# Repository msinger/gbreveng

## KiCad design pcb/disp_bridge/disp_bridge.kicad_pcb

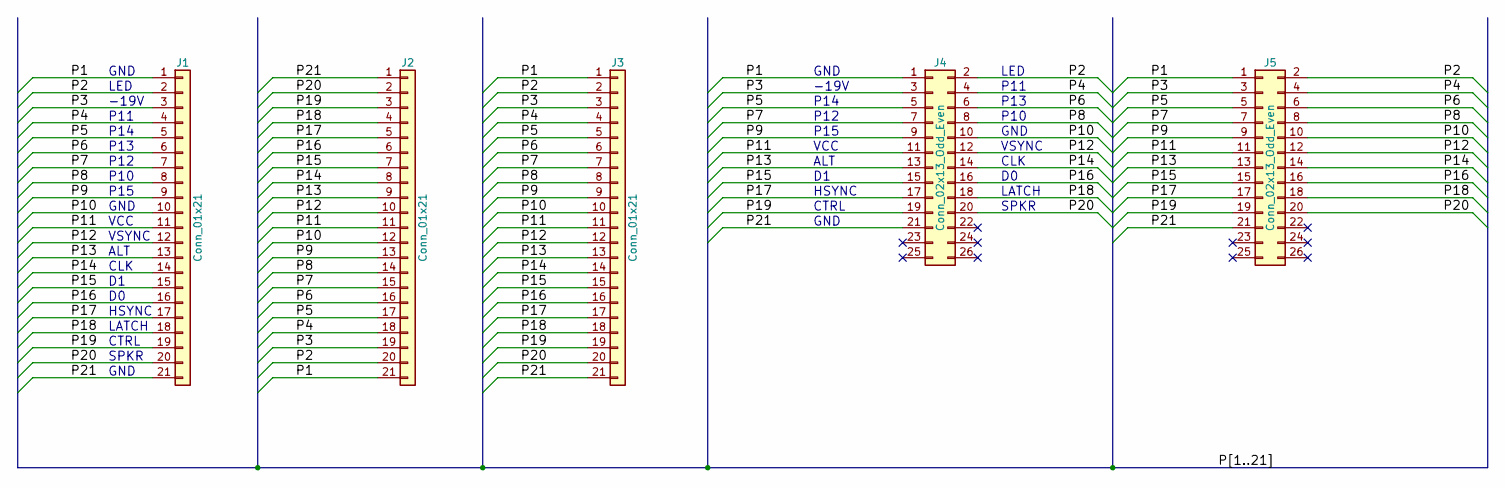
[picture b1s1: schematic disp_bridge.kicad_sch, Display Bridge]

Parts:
J1, J2, J3: Conn_01x21; DMG_FFC_LCD-Board_21Pin
J4, J5: Conn_02x13_Odd_Even; PinHeader_2x13_P2.54mm_Vertical

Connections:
/P1: J1.1, J2.21, J3.1, J4.1, J5.1
/P2: J1.2, J2.20, J3.2, J4.2, J5.2
/P3: J1.3, J2.19, J3.3, J4.3, J5.3
/P4: J1.4, J2.18, J3.4, J4.4, J5.4
/P5: J1.5, J2.17, J3.5, J4.5, J5.5
/P6: J1.6, J2.16, J3.6, J4.6, J5.6
/P7: J1.7, J2.15, J3.7, J4.7, J5.7
/P8: J1.8, J2.14, J3.8, J4.8, J5.8
/P9: J1.9, J2.13, J3.9, J4.9, J5.9
/P10: J1.10, J2.12, J3.10, J4.10, J5.10
/P11: J1.11, J2.11, J3.11, J4.11, J5.11
/P12: J1.12, J2.10, J3.12, J4.12, J5.12
/P13: J1.13, J2.9, J3.13, J4.13, J5.13
/P14: J1.14, J2.8, J3.14, J4.14, J5.14
/P15: J1.15, J2.7, J3.15, J4.15, J5.15
/P16: J1.16, J2.6, J3.16, J4.16, J5.16
/P17: J1.17, J2.5, J3.17, J4.17, J5.17
/P18: J1.18, J2.4, J3.18, J4.18, J5.18
/P19: J1.19, J2.3, J3.19, J4.19, J5.19
/P20: J1.20, J2.2, J3.20, J4.20, J5.20
/P21: J1.21, J2.1, J3.21, J4.21, J5.21

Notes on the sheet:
SPKR
LATCH
P15
VSYNC
P11
P13
GND
P14
HSYNC
P12
-19V
VCC
P10
CLK
ALT
LED
CTRL

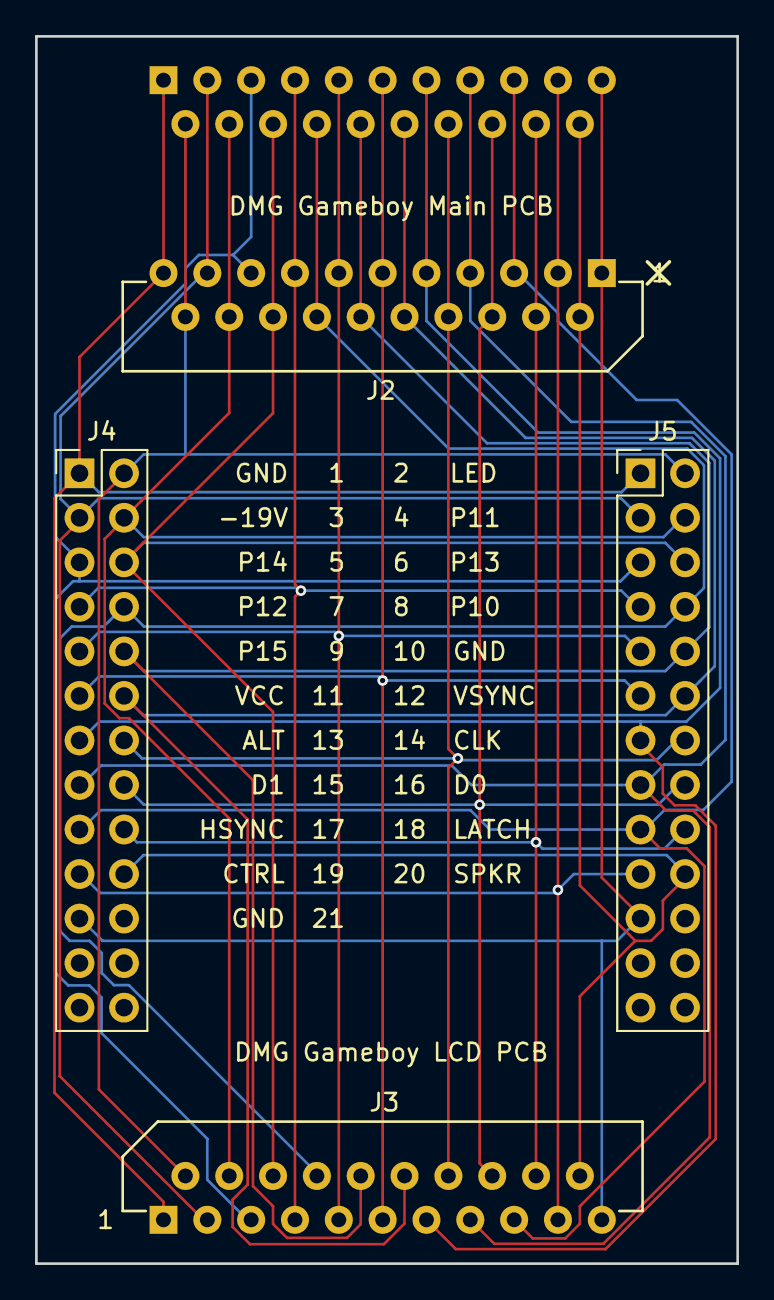
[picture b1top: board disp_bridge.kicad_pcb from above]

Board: 2 copper layers, 40.0 x 70.0 mm, 5 parts (1 on the bottom side), 21 nets.

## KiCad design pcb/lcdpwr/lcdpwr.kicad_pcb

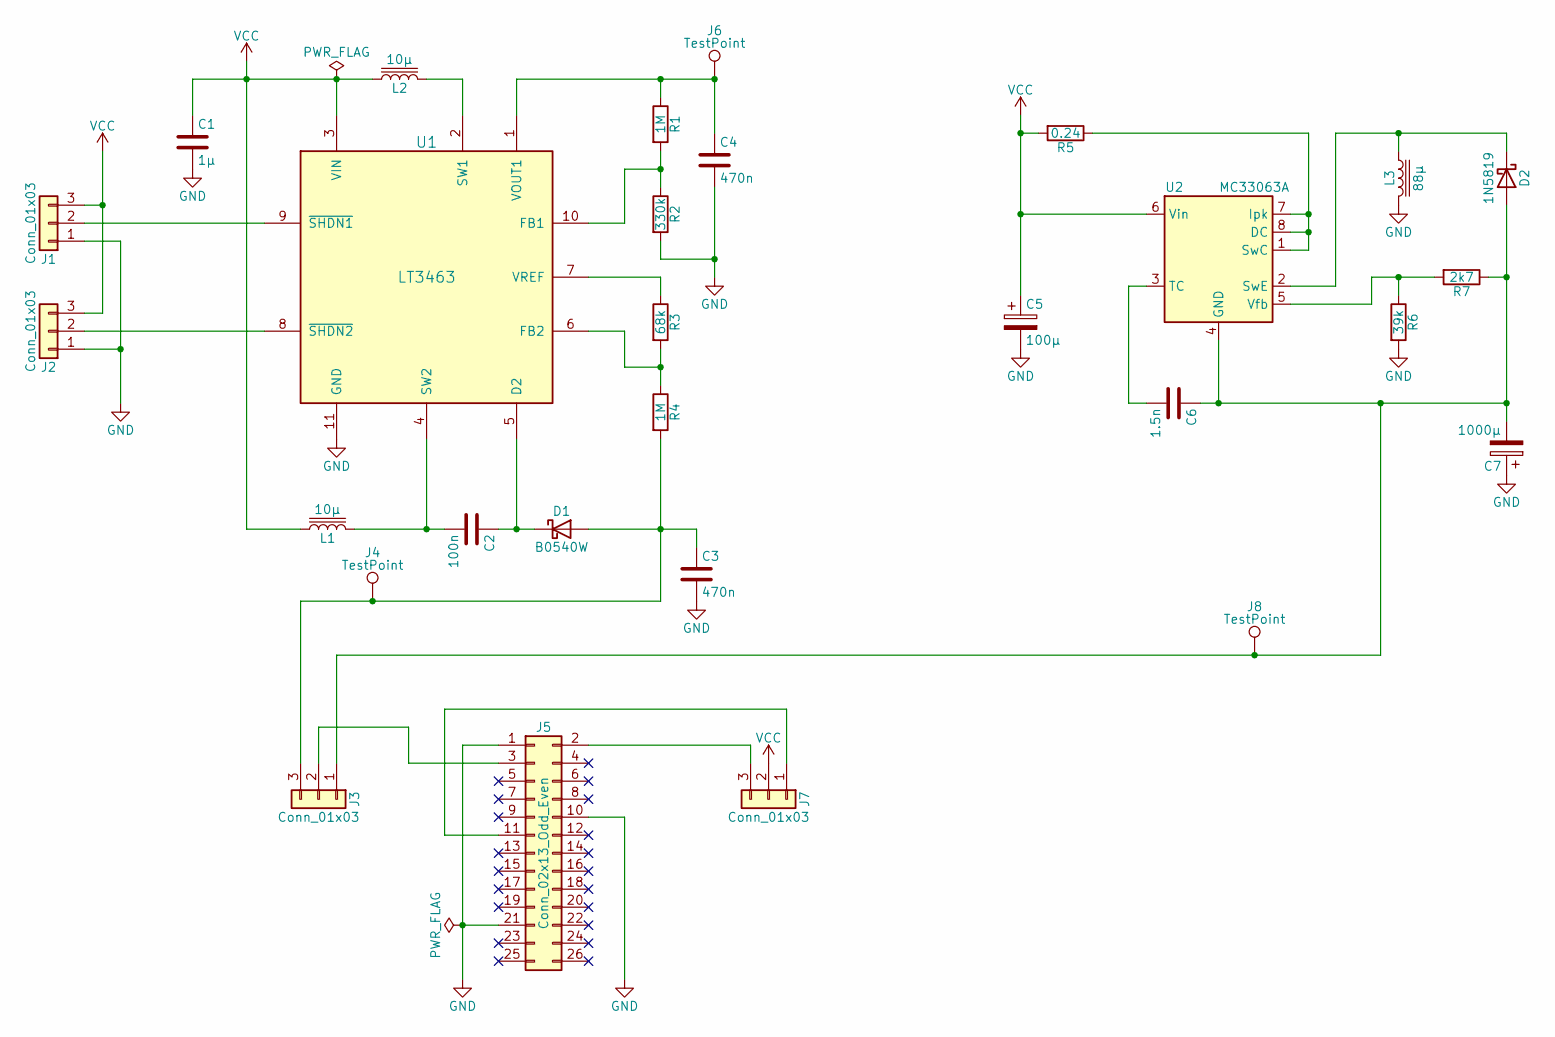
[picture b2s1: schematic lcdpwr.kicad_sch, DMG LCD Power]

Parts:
C1: 1µ; C_Disc_D4.3mm_W1.9mm_P5.00mm
C2: 100n; C_Disc_D3.0mm_W1.6mm_P2.50mm
C3, C4: 470n; C_Rect_L13.0mm_W4.0mm_P10.00mm_FKS3_FKP3_MKS4
C5: 100µ; CP_Radial_D5.0mm_P2.50mm
C6: 1.5n; C_Disc_D4.3mm_W1.9mm_P5.00mm
C7: 1000µ; CP_Radial_D10.0mm_P5.00mm
D1: B0540W; D_SOD-123
D2: 1N5819; D_A-405_P10.16mm_Horizontal
J1, J2, J3, J7: Conn_01x03; PinHeader_1x03_P2.54mm_Vertical
J4, J6, J8: TestPoint; TestPoint_Keystone_5010-5014_Multipurpose
J5: Conn_02x13_Odd_Even; PinHeader_2x13_P2.54mm_Vertical
L1, L2: 10µ; L_Radial_D7.0mm_P3.00mm
L3: 88µ; L_Radial_D12.5mm_P7.00mm_Fastron_09HCP
R1, R4: 1M; R_Axial_DIN0207_L6.3mm_D2.5mm_P10.16mm_Horizontal
R2: 330k; R_Axial_DIN0207_L6.3mm_D2.5mm_P10.16mm_Horizontal
R3: 68k; R_Axial_DIN0207_L6.3mm_D2.5mm_P10.16mm_Horizontal
R5: 0.24; R_Axial_DIN0411_L9.9mm_D3.6mm_P12.70mm_Horizontal
R6: 39k; R_Axial_DIN0207_L6.3mm_D2.5mm_P10.16mm_Horizontal
R7: 2k7; R_Axial_DIN0207_L6.3mm_D2.5mm_P10.16mm_Horizontal
U1: LT3463; DFN-10-1EP_3x3mm_P0.5mm_EP1.55x2.48mm
U2: MC33063A; DIP-8_W7.62mm_Socket_LongPads

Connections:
GND: C1.2, C3.2, C4.2, C5.2, C7.1, J1.1, J2.1, J5.1, J5.10, J5.21, L3.2, R2.2, R6.2, U1.11 (GND)
unnamed: C3.1, D1.2 (A), J3.3, J4.1, R4.2
unnamed: C2.1, D1.1 (K), U1.5 (D2)
unnamed: C6.1, C7.2, D2.2 (A), J3.1, J8.1, R7.1, U2.4 (GND)
unnamed: D2.1 (K), L3.1, U2.2 (SwE)
unnamed: J1.2, U1.9 (~SHDN1)
unnamed: J2.2, U1.8 (~SHDN2)
unnamed: J3.2, J5.3
unnamed: J5.2, J7.3
unnamed: J5.11, J7.1
unnamed: R1.2, R2.1, U1.10 (FB1)
unnamed: R3.2, R4.1, U1.6 (FB2)
unnamed: L2.2, U1.2 (SW1)
unnamed: C2.2, L1.2, U1.4 (SW2)
unnamed: C4.1, J6.1, R1.1, U1.1 (VOUT1)
unnamed: R3.1, U1.7 (VREF)
unnamed: R5.1, U2.1 (SwC), U2.7 (Ipk), U2.8 (DC)
unnamed: C6.2, U2.3 (TC)
unnamed: R6.1, R7.2, U2.5 (Vfb)
VCC: C1.1, C5.1, J1.3, J2.3, J7.2, L1.1, L2.1, R5.2, U1.3 (VIN), U2.6 (Vin)

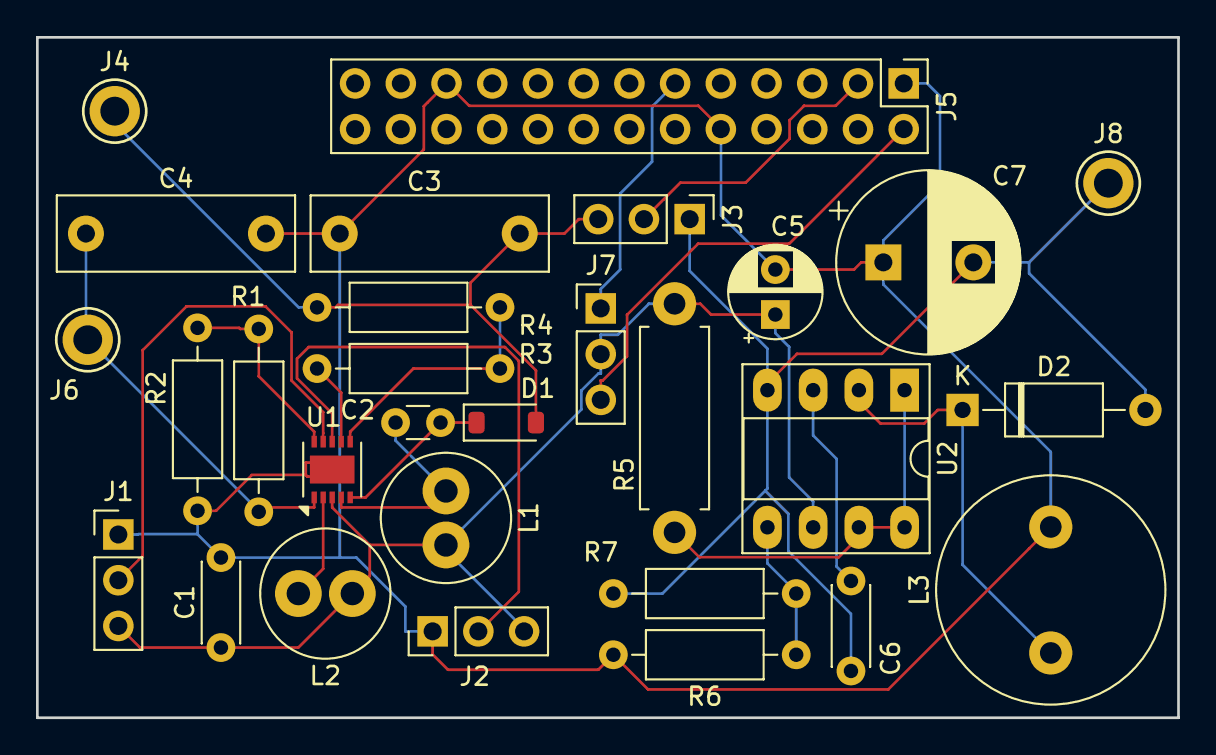
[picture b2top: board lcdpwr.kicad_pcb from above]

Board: 2 copper layers, 63.4 x 37.8 mm, 29 parts (0 on the bottom side), 20 nets.

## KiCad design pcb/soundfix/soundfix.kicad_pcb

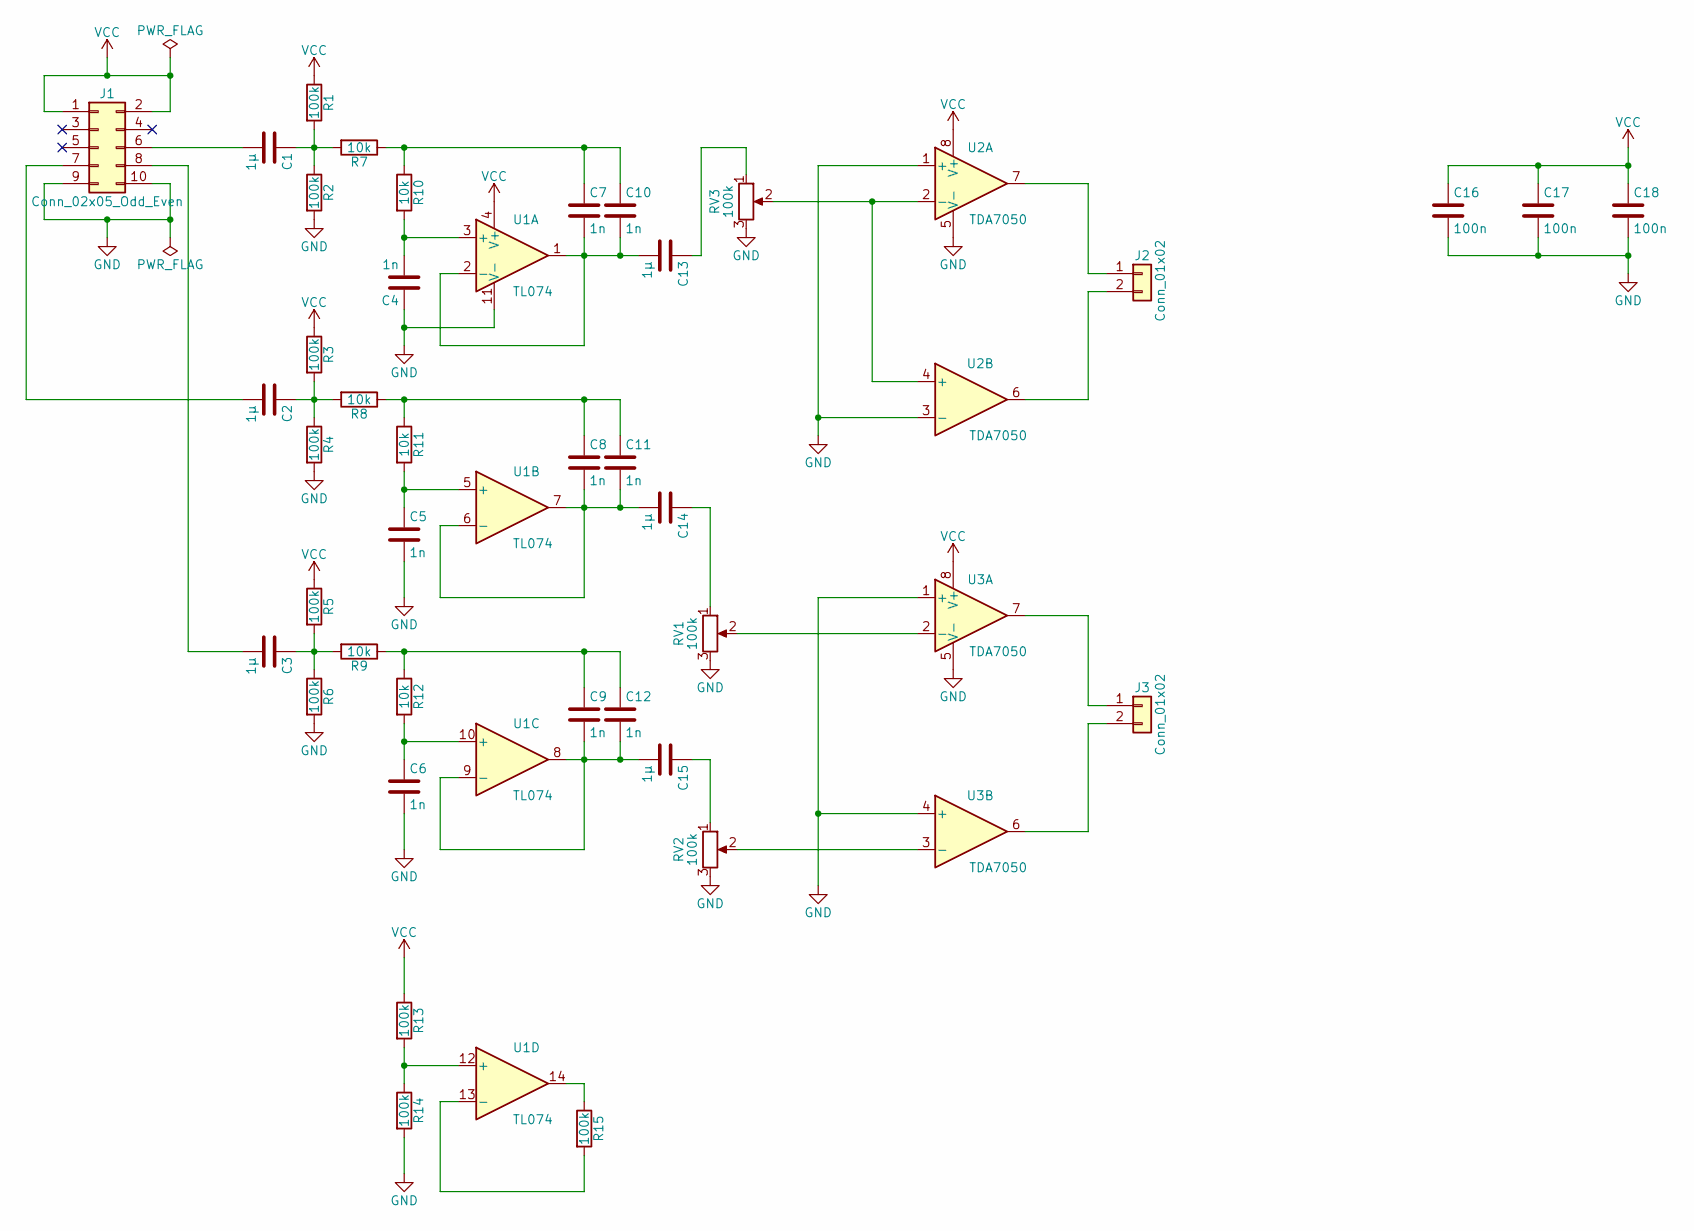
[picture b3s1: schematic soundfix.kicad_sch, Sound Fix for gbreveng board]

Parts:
C1, C2, C3, C13, C14, C15: 1µ; C_Disc_D5.0mm_W2.5mm_P5.00mm
C4, C5, C6, C7, C8, C9, C10, C11, C12: 1n; C_Disc_D3.0mm_W2.0mm_P2.50mm
C16, C17, C18: 100n; C_Disc_D3.0mm_W2.0mm_P2.50mm
J1: Conn_02x05_Odd_Even; PinSocket_2x05_P2.54mm_Vertical
J2, J3: Conn_01x02; PinHeader_1x02_P2.54mm_Vertical
R1, R2, R3, R4, R5, R6, R13, R14, R15: 100k; R_Axial_DIN0207_L6.3mm_D2.5mm_P2.54mm_Vertical
R7, R8, R9, R10, R11, R12: 10k; R_Axial_DIN0207_L6.3mm_D2.5mm_P2.54mm_Vertical
RV1, RV2, RV3: 100k; Potentiometer_ACP_CA9-H2,5_Horizontal
U1: TL074; DIP-14_W7.62mm_Socket
U2, U3: TDA7050; DIP-8_W7.62mm_Socket

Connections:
GND: C4.1, C5.2, C6.2, C16.2, C17.2, C18.2, J1.9, J1.10, R2.2, R4.2, R6.2, R14.2, RV1.3, RV2.3, RV3.3, U1.11 (V-), U2.1 (+), U2.3 (-), U2.5 (V-), U3.1 (+), U3.4 (+), U3.5 (V-)
unnamed: C1.1, R1.2, R2.1, R7.2
unnamed: C2.1, R3.2, R4.1, R8.2
unnamed: C3.1, R5.2, R6.1, R9.2
unnamed: C7.1, C10.1, R7.1, R10.1
unnamed: C8.1, C11.1, R8.1, R11.1
unnamed: C9.1, C12.1, R9.1, R12.1
unnamed: C13.1, RV3.1
unnamed: C14.1, RV1.1
unnamed: C15.1, RV2.1
unnamed: C1.2, J1.6
unnamed: C2.2, J1.7
unnamed: C3.2, J1.8
unnamed: J2.1, U2.7
unnamed: J2.2, U2.6
unnamed: J3.1, U3.7
unnamed: J3.2, U3.6
unnamed: R15.1, U1.14
unnamed: C4.2, R10.2, U1.3 (+)
unnamed: C7.2, C10.2, C13.2, U1.1, U1.2 (-)
unnamed: C5.1, R11.2, U1.5 (+)
unnamed: C8.2, C11.2, C14.2, U1.6 (-), U1.7
unnamed: C6.1, R12.2, U1.10 (+)
unnamed: C9.2, C12.2, C15.2, U1.8, U1.9 (-)
unnamed: R13.2, R14.1, U1.12 (+)
unnamed: R15.2, U1.13 (-)
unnamed: RV3.2, U2.2 (-), U2.4 (+)
unnamed: RV1.2, U3.2 (-)
unnamed: RV2.2, U3.3 (-)
VCC: C16.1, C17.1, C18.1, J1.1, J1.2, R1.1, R3.1, R5.1, R13.1, U1.4 (V+), U2.8 (V+), U3.8 (V+)

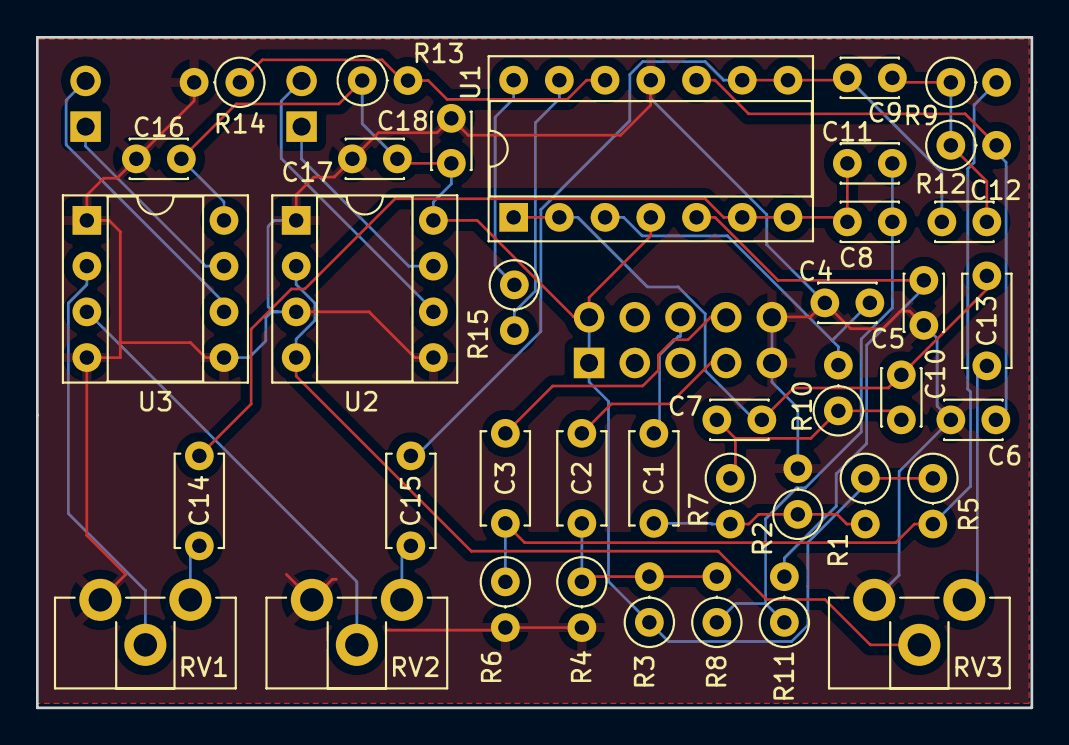
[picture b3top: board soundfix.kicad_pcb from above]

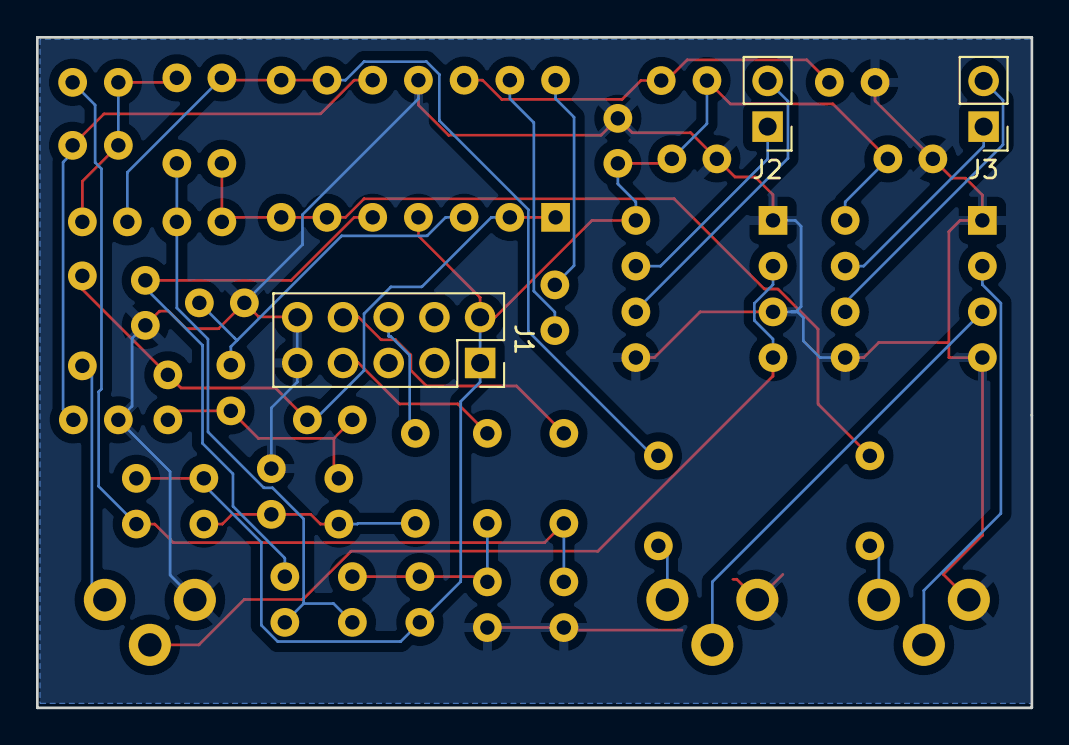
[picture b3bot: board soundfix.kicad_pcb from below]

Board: 2 copper layers, 55.2 x 37.2 mm, 42 parts (3 on the bottom side), 30 nets.

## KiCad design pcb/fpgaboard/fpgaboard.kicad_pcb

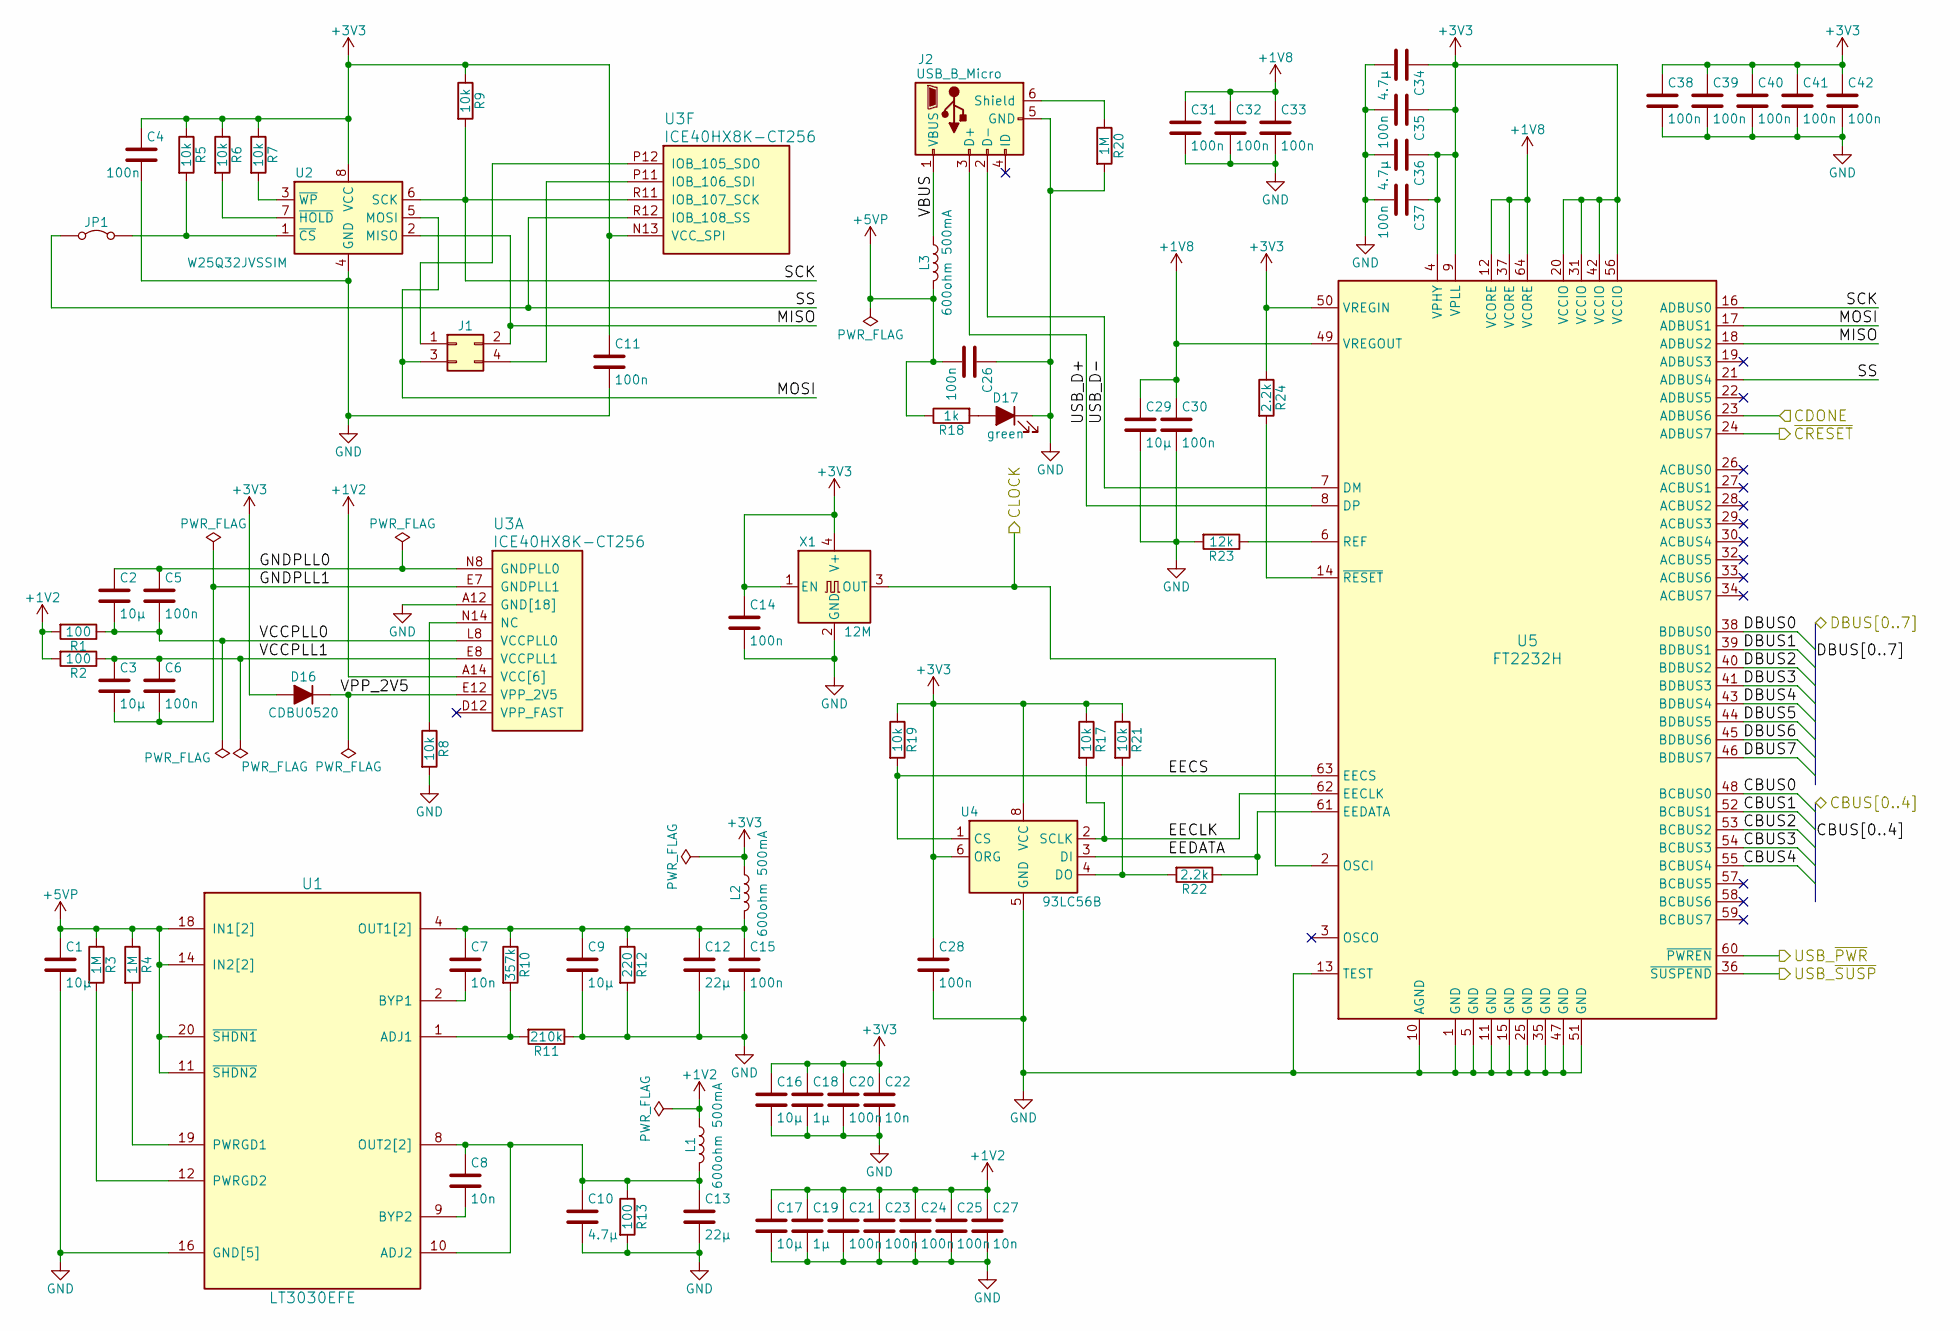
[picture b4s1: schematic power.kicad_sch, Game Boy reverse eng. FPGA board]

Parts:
C1, C2, C3, C9, C16, C17, C29: 10µ; C_0603_1608Metric
C4, C5, C6, C11, C14, C15, C20, C25, C26, C28, C30, C31, C32, C33, C35, C37, C38, C39, C40, C41, C42: 100n; C_0402_1005Metric_Pad0.74x0.62mm_HandSolder
C7, C8, C22: 10n; C_0402_1005Metric_Pad0.74x0.62mm_HandSolder
C10, C34, C36: 4.7µ; C_0603_1608Metric
C12, C13: 22µ; C_0805_2012Metric
C18, C19: 1µ; C_0402_1005Metric_Pad0.74x0.62mm_HandSolder
C21, C23, C24: 100n; C_0402_1005Metric
C27: 10n; C_0402_1005Metric
D16: CDBU0520; D_0603_1608Metric
D17: green; LED_0805_2012Metric_Pad1.15x1.40mm_HandSolder
J1: Conn_02x02_Odd_Even; PinHeader_2x02_P2.54mm_Vertical
J2: USB_B_Micro; USB_Micro-B_Molex-105017-0001
JP1: Jumper_2_Bridged; PinHeader_1x02_P2.54mm_Vertical
L1, L2, L3: 600ohm 500mA; L_0603_1608Metric
R1, R2, R13: 100; R_0805_2012Metric
R3, R4, R20: 1M; R_0402_1005Metric
R5, R6, R7, R8, R9, R17, R19, R21: 10k; R_0402_1005Metric
R10: 357k; R_0402_1005Metric
R11: 210k; R_0402_1005Metric
R12: 220; R_0805_2012Metric
R18: 1k; R_0402_1005Metric
R22, R24: 2.2k; R_0402_1005Metric
R23: 12k; R_0402_1005Metric
U1: LT3030EFE; ETSSOP-20-1EP_4.4x6.5mm_P0.65mm_EP3x4.2mm
U2: W25Q32JVSSIM; SOIC-8W_5.3x5.3mm_P1.27mm
U3: ICE40HX8K-CT256; BGA-256_14.0x14.0mm_Layout16x16_P0.8mm_Ball0.45mm_Pad0.32mm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
U4: 93LC56B; SOIC-8_3.9x4.9mm_P1.27mm
U5: FT2232H; LQFP-64_10x10mm_P0.5mm
X1: 12M; Oscillator_SMD_EuroQuartz_XO32-4Pin_3.2x2.5mm_HandSoldering

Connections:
+1V2: C17.1, C19.1, C21.1, C23.1, C24.1, C25.1, C27.1, L1.1, R1.2, R2.2, U3.A14 (VCC[6]), U3.F6 (VCC[6]), U3.F10 (VCC[6]), U3.K6 (VCC[6]), U3.K10 (VCC[6]), U3.L2 (VCC[6])
+1V8: C29.1, C30.1, C31.1, C32.1, C33.1, U5.12 (VCORE), U5.37 (VCORE), U5.49 (VREGOUT), U5.64 (VCORE)
+3V3: C4.1, C11.1, C14.1, C16.1, C18.1, C20.1, C22.1, C28.1, C34.1, C35.1, C36.1, C37.1, C38.1, C39.1, C40.1, C41.1, C42.1, D16.2 (A), L2.1, R5.1, R6.1, R7.1, R9.1, R17.1, R19.1, R21.1, R24.1, U2.8 (VCC), U3.N13 (VCC_SPI), U4.6 (ORG), U4.8 (VCC), U5.4 (VPHY), U5.9 (VPLL), U5.20 (VCCIO), U5.31 (VCCIO), U5.42 (VCCIO), U5.50 (VREGIN), U5.56 (VCCIO), X1.1 (EN), X1.4 (V+); also elsewhere on the board
+5VP: C1.1, C26.2, L3.1, R3.1, R4.1, R18.1, U1.11 (~SHDN2), U1.13 (IN2[2]), U1.14 (IN2[2]), U1.17 (IN1[2]), U1.18 (IN1[2]), U1.20 (~SHDN1); also elsewhere on the board
/Bank0: Display, Keyboard, Clock/CBUS0: U5.48 (BCBUS0); also elsewhere on the board
/Bank0: Display, Keyboard, Clock/CBUS1: U5.52 (BCBUS1); also elsewhere on the board
/Bank0: Display, Keyboard, Clock/CBUS2: U5.53 (BCBUS2); also elsewhere on the board
/Bank0: Display, Keyboard, Clock/CBUS3: U5.54 (BCBUS3); also elsewhere on the board
/Bank0: Display, Keyboard, Clock/CBUS4: U5.55 (BCBUS4); also elsewhere on the board
/Bank0: Display, Keyboard, Clock/DBUS0: U5.38 (BDBUS0); also elsewhere on the board
/Bank0: Display, Keyboard, Clock/DBUS1: U5.39 (BDBUS1); also elsewhere on the board
/Bank0: Display, Keyboard, Clock/DBUS2: U5.40 (BDBUS2); also elsewhere on the board
/Bank0: Display, Keyboard, Clock/DBUS3: U5.41 (BDBUS3); also elsewhere on the board
/Bank0: Display, Keyboard, Clock/DBUS4: U5.43 (BDBUS4); also elsewhere on the board
/Bank0: Display, Keyboard, Clock/DBUS5: U5.44 (BDBUS5); also elsewhere on the board
/Bank0: Display, Keyboard, Clock/DBUS6: U5.45 (BDBUS6); also elsewhere on the board
/Bank0: Display, Keyboard, Clock/DBUS7: U5.46 (BDBUS7); also elsewhere on the board
/Bank0: Display, Keyboard, Clock/USB_~PWR: U5.60 (~PWREN); also elsewhere on the board
/Bank0: Display, Keyboard, Clock/USB_~SUSP: U5.36 (~SUSPEND); also elsewhere on the board
/Bank2: SDCard/CDONE: U5.23 (ADBUS6); also elsewhere on the board
/Bank2: SDCard/~CRESET: U5.24 (ADBUS7); also elsewhere on the board
/Bank3: LEDs, Switches/CLOCK: U5.2 (OSCI), X1.3 (OUT); also elsewhere on the board
/Power, USB, SPI/EECLK: R17.2, U4.2 (SCLK), U5.62 (EECLK)
/Power, USB, SPI/EECS: R19.2, U4.1 (CS), U5.63 (EECS)
/Power, USB, SPI/EEDATA: R22.1, U4.3 (DI), U5.61 (EEDATA)
/Power, USB, SPI/GNDPLL0: C2.1, C5.1, U3.N8 (GNDPLL0)
/Power, USB, SPI/GNDPLL1: C3.2, C6.2, U3.E7 (GNDPLL1)
/Power, USB, SPI/MISO: J1.2, U2.2 (MISO), U5.18 (ADBUS2)
/Power, USB, SPI/MOSI: J1.3, U2.5 (MOSI), U5.17 (ADBUS1)
/Power, USB, SPI/SCK: R9.2, U2.6 (SCK), U3.R11 (IOB_107_SCK), U5.16 (ADBUS0)
/Power, USB, SPI/SS: JP1.1 (A), U3.R12 (IOB_108_SS), U5.21 (ADBUS4)
/Power, USB, SPI/USB_D+: J2.3 (D+), U5.8 (DP)
/Power, USB, SPI/USB_D-: J2.2 (D-), U5.7 (DM)
/Power, USB, SPI/VBUS: J2.1 (VBUS), L3.2
/Power, USB, SPI/VCCPLL0: C2.2, C5.2, R1.1, U3.L8 (VCCPLL0)
/Power, USB, SPI/VCCPLL1: C3.1, C6.1, R2.1, U3.E8 (VCCPLL1)
/Power, USB, SPI/VPP_2V5: D16.1 (K), U3.E12 (VPP_2V5)
GND: C1.2, C4.2, C9.2, C10.2, C11.2, C12.2, C13.2, C14.2, C15.2, C16.2, C17.2, C18.2, C19.2, C20.2, C21.2, C22.2, C23.2, C24.2, C25.2, C26.1, C27.2, C28.2, C29.2, C30.2, C31.2, C32.2, C33.2, C34.2, C35.2, C36.2, C37.2, C38.2, C39.2, C40.2, C41.2, C42.2, D17.1 (K), J2.5 (GND), R8.2, R11.1, R12.2, R13.2, R20.2, R23.2, U1.5 (GND[5]), U1.6 (GND[5]), U1.15 (GND[5]), U1.16 (GND[5]), U1.21 (GND[5]), U2.4 (GND), U3.A4 (GND[18]), U3.A12 (GND[18]), U3.E15 (GND[18]), U3.G7 (GND[18]), U3.G8 (GND[18]), U3.G9 (GND[18]), U3.H7 (GND[18]), U3.H8 (GND[18]), U3.H9 (GND[18]), U3.J7 (GND[18]), U3.J8 (GND[18]), U3.J9 (GND[18]), U3.K2 (GND[18]), U3.K7 (GND[18]), U3.L15 (GND[18]), U3.R7 (GND[18]), U3.T4 (GND[18]), U3.T12 (GND[18]), U4.5 (GND), U5.1 (GND), U5.5 (GND), U5.10 (AGND), U5.11 (GND), U5.13 (TEST), U5.15 (GND), U5.25 (GND), U5.35 (GND), U5.47 (GND), U5.51 (GND), X1.2 (GND); also elsewhere on the board
unnamed: C7.2, U1.2 (BYP1)
unnamed: C8.2, U1.9 (BYP2)
unnamed: C8.1, C10.1, C13.1, L1.2, R13.1, U1.7 (OUT2[2]), U1.8 (OUT2[2]), U1.10 (ADJ2)
unnamed: C7.1, C9.1, C12.1, C15.1, L2.2, R10.1, R12.1, U1.3 (OUT1[2]), U1.4 (OUT1[2])
unnamed: D17.2 (A), R18.2
unnamed: J1.1, U3.P12 (IOB_105_SDO)
unnamed: J1.4, U3.P11 (IOB_106_SDI)
unnamed: J2.6 (Shield), R20.1
unnamed: JP1.2 (B), R5.2, U2.1 (~CS)
unnamed: R3.2, U1.12 (PWRGD2)
unnamed: R4.2, U1.19 (PWRGD1)
unnamed: R6.2, U2.7 (~HOLD)
unnamed: R7.2, U2.3 (~WP)
unnamed: R8.1, U3.N14 (NC)
unnamed: R10.2, R11.2, U1.1 (ADJ1)
unnamed: R21.2, R22.2, U4.4 (DO)
unnamed: R23.1, U5.6 (REF)
unnamed: R24.2, U5.14 (~RESET)

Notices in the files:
pcb/fpgaboard/audio.kicad_sch:
CC-BY-SA-4.0 Michael Singer
